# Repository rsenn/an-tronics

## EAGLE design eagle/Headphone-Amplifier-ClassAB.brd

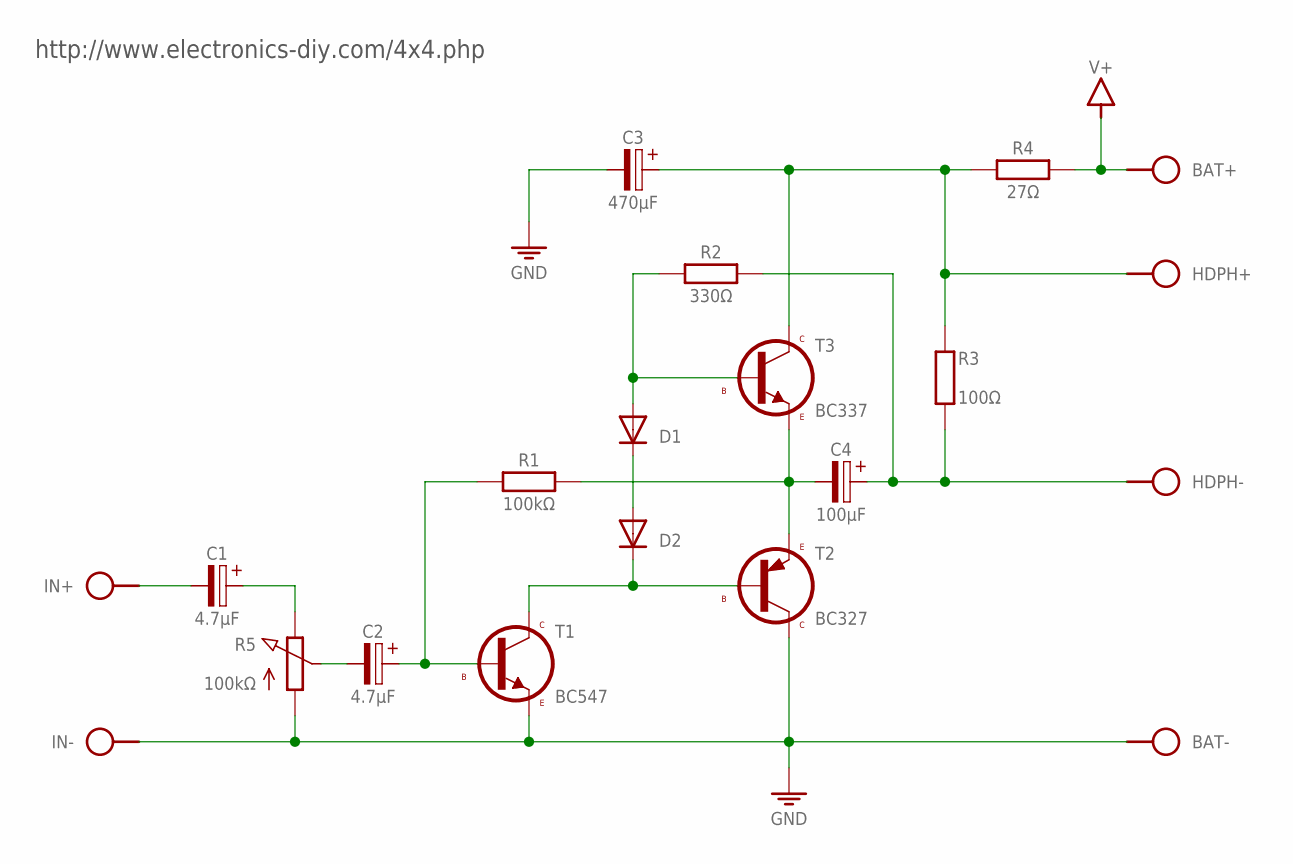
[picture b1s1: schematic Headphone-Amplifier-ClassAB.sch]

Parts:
BAT: SPAD+-+-; SPAD+-
C1, C2: 4.7μF; E2,5-4
C3: 470μF; E5-6
C4: 100μF; E5-4
D1, D2: 1N414834-5V; DO34-5V
HDPH: SPAD+--+; SPAD-+
IN: SPAD+--+; SPAD-+
R1: 100kΩ; 0202/7
R2: 330Ω; 0204/10
R3: 100Ω; 0204/10
R4: 27Ω; 0204V
R5: 100kΩ; CONN-3P
T1: BC547; TO92
T2: BC327; TO92
T3: BC337; TO92-CBE

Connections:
GND: BAT.1, C3.-, IN.1, R5.1 (A), T1.3 (E), T2.1 (C)
unnamed: D1.A, R2.1, T3.2 (B)
unnamed: D2.C, T1.1 (C), T2.2 (B)
unnamed: D1.C, D2.A
unnamed: C4.-, R1.2, T2.3 (E), T3.3 (E)
unnamed: C1.+, R5.3 (E)
unnamed: C2.-, R5.2 (S)
unnamed: C2.+, R1.1, T1.2 (B)
unnamed: C3.+, HDPH.2, R3.2 (1), R4.2 (1), T3.1 (C)
unnamed: C4.+, HDPH.1, R2.2, R3.1 (2)
unnamed: C1.-, IN.2
V+: BAT.2, R4.1 (2)

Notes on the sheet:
http://www.electronics-diy.com/4x4.php

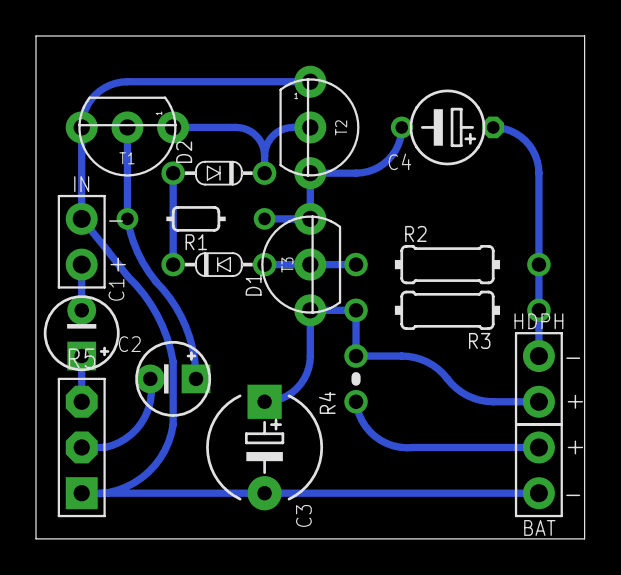
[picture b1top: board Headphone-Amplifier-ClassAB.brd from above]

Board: 2 copper layers, 30.5 x 27.9 mm, 17 parts (0 on the bottom side), 12 nets.

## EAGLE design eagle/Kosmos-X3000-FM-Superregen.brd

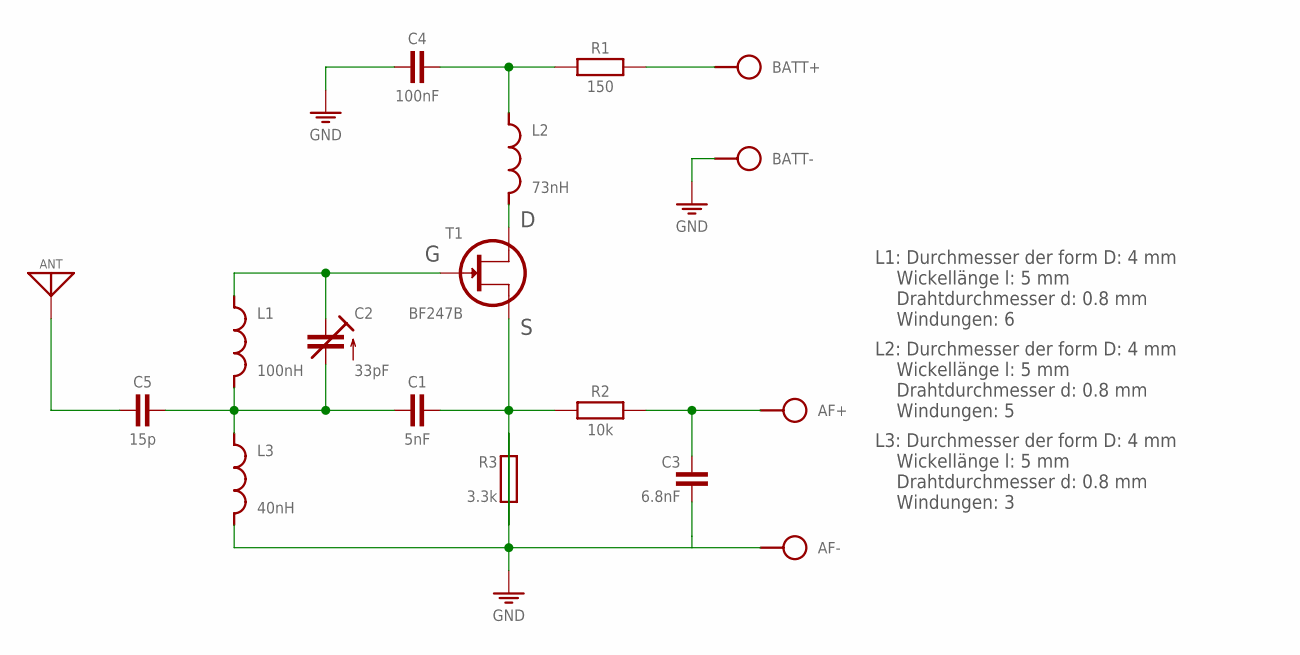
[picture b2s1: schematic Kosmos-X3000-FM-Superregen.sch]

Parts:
AF: SPAD+-+-; SPAD+-
ANT: ANT; SPAD
BATT: SPAD+-+-; SPAD+-
C1: 5nF; C050-020X044
C2: 33pF; TRIM-2222-808
C3: 6.8nF; C050-020X044
C4: 100nF; C050-020X044
C5: 15p; C025-015X024
L1: 100nH; L-04-5/5V
L2: 73nH; L-04-5/5V
L3: 40nH; L-04-5/5V
R1: 150; 0202/7-V
R2: 10k; 0202/7
R3: 3.3k; 0202/7
T1: BF247B; TO92

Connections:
GND: AF.1, BATT.1, C3.2, C4.2, L3.1, R3.2 (1)
unnamed: C2.1 (E), L1.2, T1.3 (G)
unnamed: C1.2, C2.2 (A), C5.1, L1.1, L3.2
unnamed: C4.1, L2.2, R1.1
unnamed: AF.2, C3.1, R2.2
unnamed: C1.1, R2.1, R3.1 (2), T1.2 (S)
unnamed: L2.1, T1.1 (D)
unnamed: BATT.2, R1.2
unnamed: ANT.1, C5.2

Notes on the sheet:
L2: Durchmesser der form D: 4 mm Wickellänge l: 5 mm Drahtdurchmesser d: 0.8 mm Windungen: 5
L3: Durchmesser der form D: 4 mm Wickellänge l: 5 mm Drahtdurchmesser d: 0.8 mm Windungen: 3
L1: Durchmesser der form D: 4 mm Wickellänge l: 5 mm Drahtdurchmesser d: 0.8 mm Windungen: 6

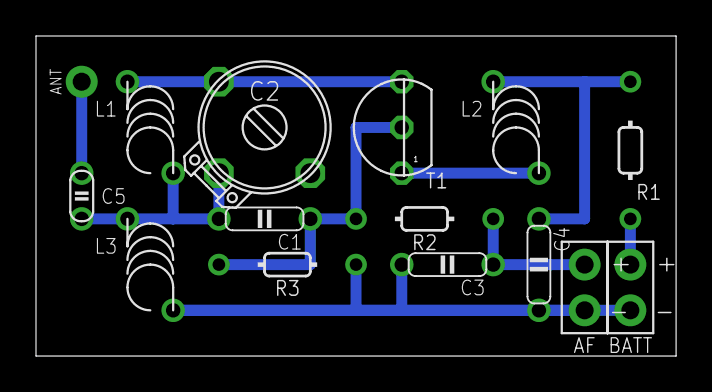
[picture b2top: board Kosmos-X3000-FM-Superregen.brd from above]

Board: 2 copper layers, 35.6 x 17.8 mm, 15 parts (0 on the bottom side), 9 nets.

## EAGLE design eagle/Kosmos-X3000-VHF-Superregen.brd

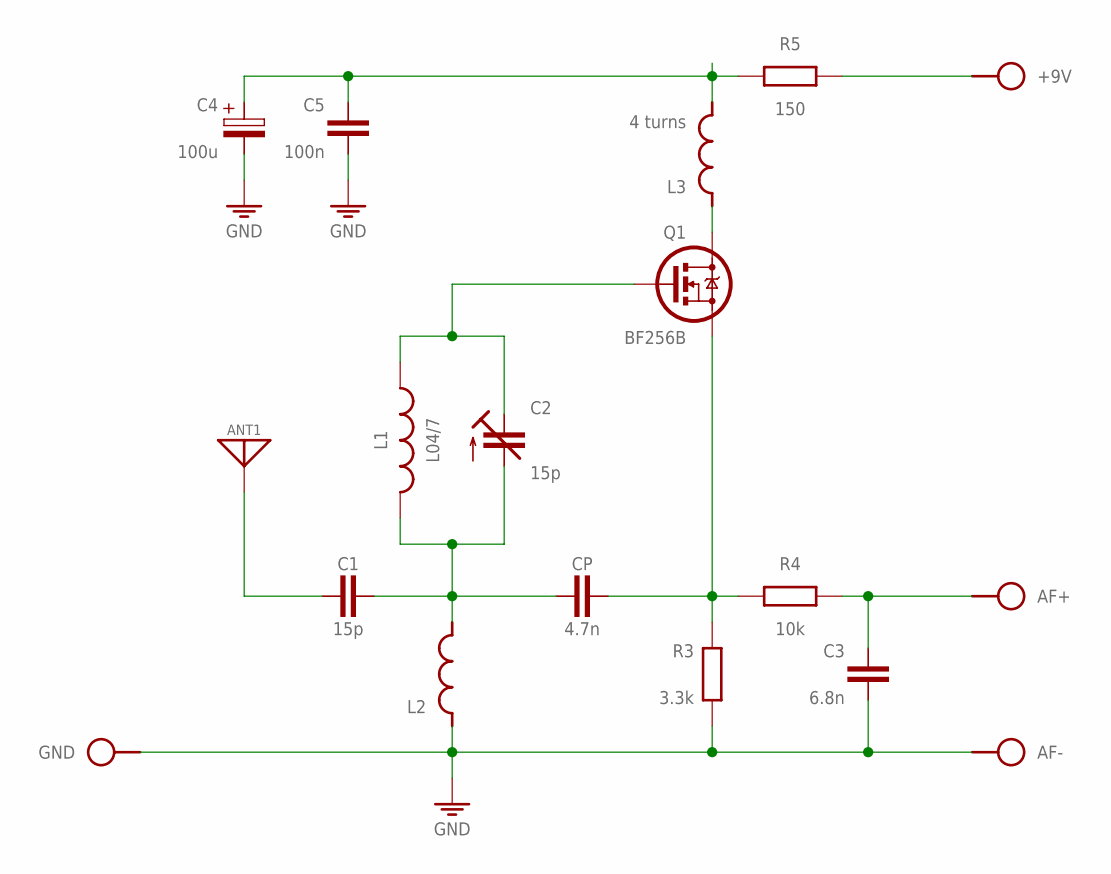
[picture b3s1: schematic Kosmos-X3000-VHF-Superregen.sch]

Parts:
+9V: SPAD
AF+: SPAD
AF-: SPAD
ANT1: ANT; SPAD
C1: 15p; C025-015X024
C2: 15p; TRIM-2222-808
C3: 6.8n; C050-020X036
C4: 100u; E2.5-4/V
C5: 100n; C025-015X024
CP: 4.7n; C025-015X024
GND: SPAD
L1: L04/7; L-04/7V
L2: L-SHORT04-5/5V; L-04-5/5V
L3: 4 turns; L-04-5/5V
Q1: BF256B; TO92
R3: 3.3k; 0204/10
R4: 10k; 0204/10
R5: 150; 0204/10

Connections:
GND: AF-.1, C3.2, C4.-, C5.2, GND.1, L2.2, R3.1
unnamed: CP.1, Q1.2 (S), R3.2, R4.1
unnamed: AF+.1, C3.1, R4.2
unnamed: ANT1.1, C1.2
unnamed: C4.+, C5.1, L3.1, R5.1
unnamed: C2.3 (E), L1.2 (1), Q1.1 (G)
unnamed: C1.1, C2.2 (A), CP.2, L1.1 (2), L2.1
unnamed: L3.2, Q1.3 (D)
unnamed: +9V.1, R5.2

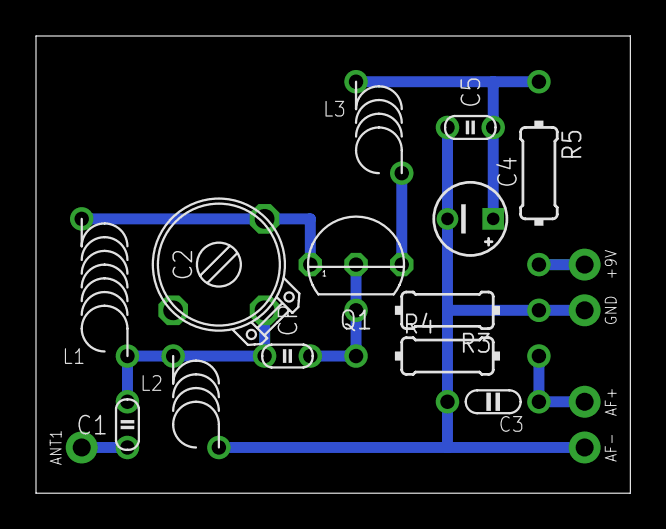
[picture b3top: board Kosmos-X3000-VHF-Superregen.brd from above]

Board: 2 copper layers, 33.0 x 25.4 mm, 18 parts (0 on the bottom side), 9 nets.

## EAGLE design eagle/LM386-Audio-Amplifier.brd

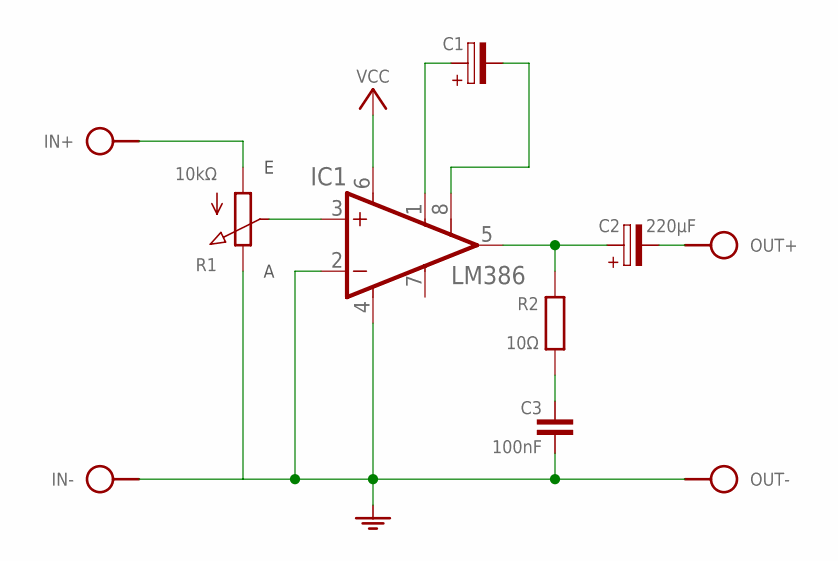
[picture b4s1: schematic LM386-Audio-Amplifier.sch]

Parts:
C1: CPOL-HE2,5-3; E2,5-3
C2: 220µF; E5-5
C3: 100nF; C050-020X044
IC1: LM386; DIL08
IN: SPAD+-+-; SPAD+-
OUT: SPAD+--+; SPAD-+
R1: 10kΩ; CONN-3P
R2: 10Ω; 0204/10-V
S1: 4-12V; PWR-R

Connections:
GND: C3.2, IC1.2 (-IN), IC1.4 (GND), IN.1, OUT.1, R1.3 (E), S1.1 (GND)
unnamed: IC1.3 (+IN), R1.2 (S)
unnamed: IN.2, R1.1 (A)
unnamed: C1.+, IC1.1 (GAIN)
unnamed: C1.-, IC1.8 (GAIN)
unnamed: C3.1, R2.2 (1)
unnamed: C2.+, IC1.5 (OUT), R2.1 (2)
unnamed: C2.-, OUT.2
VCC: IC1.6 (VS), S1.2 (VCC)

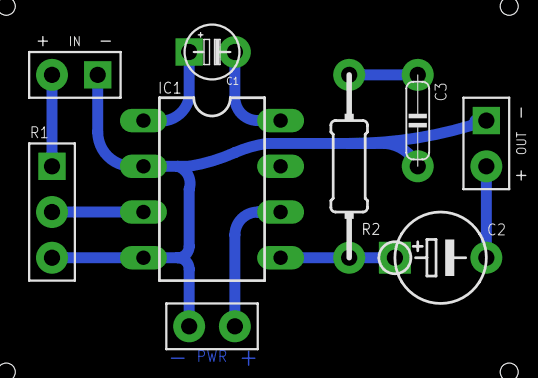
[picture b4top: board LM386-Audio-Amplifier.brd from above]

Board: 2 copper layers, 9 parts (0 on the bottom side), 9 nets.

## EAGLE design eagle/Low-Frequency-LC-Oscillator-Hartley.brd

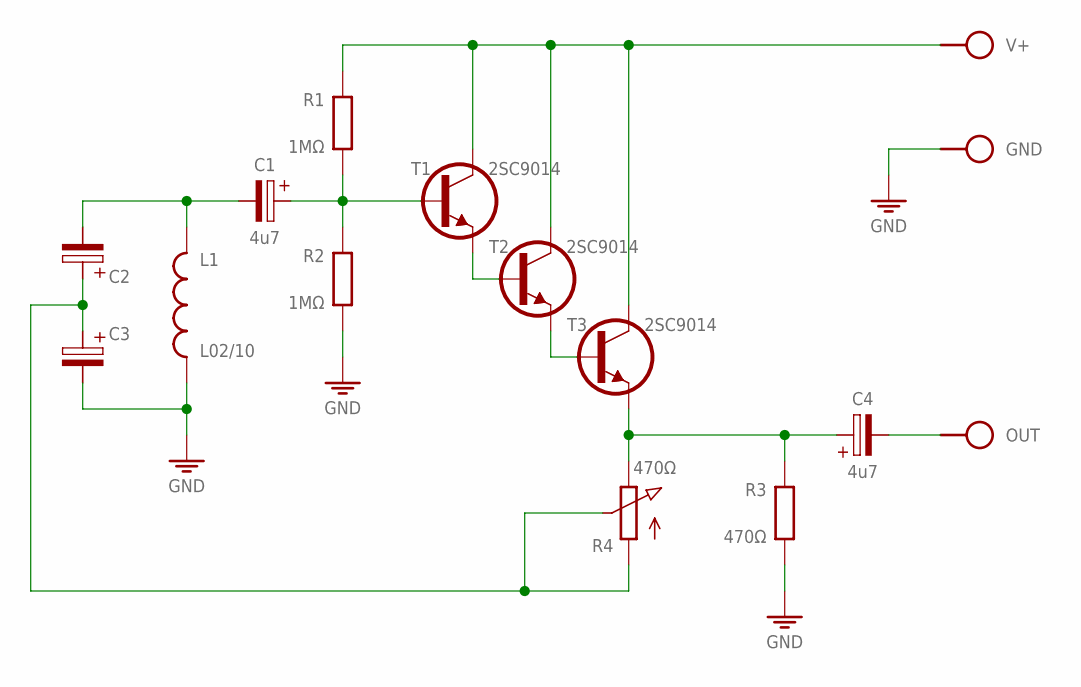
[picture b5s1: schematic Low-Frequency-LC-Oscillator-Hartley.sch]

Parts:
C1, C4: 4u7; E2,5-3
C2, C3: CPOLE2.5-5; E2,5-5
GND: SPAD
L1: L02/10; L-03/10V
OUT: SPAD
R1: 1MΩ; 0204/15
R2: 1MΩ; 0204/12-V
R3: 470Ω; 0204/12
R4: 470Ω; POT
T1, T2, T3: 2SC9014; TO92-EBC
V+: SPAD

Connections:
GND: C3.-, GND.1, L1.2, R2.1, R3.1
unnamed: R1.2, T1.C, T2.C, T3.C, V+.1
unnamed: C4.-, OUT.1
unnamed: C4.+, R3.2, R4.3 (E), T3.E
unnamed: T1.E, T2.B
unnamed: T2.E, T3.B
unnamed: C1.-, C2.-, L1.1
unnamed: C1.+, R1.1, R2.2, T1.B
unnamed: C2.+, C3.+, R4.1 (A), R4.2 (S)

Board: 2 copper layers, 15 parts (0 on the bottom side), 9 nets, no tracks yet.

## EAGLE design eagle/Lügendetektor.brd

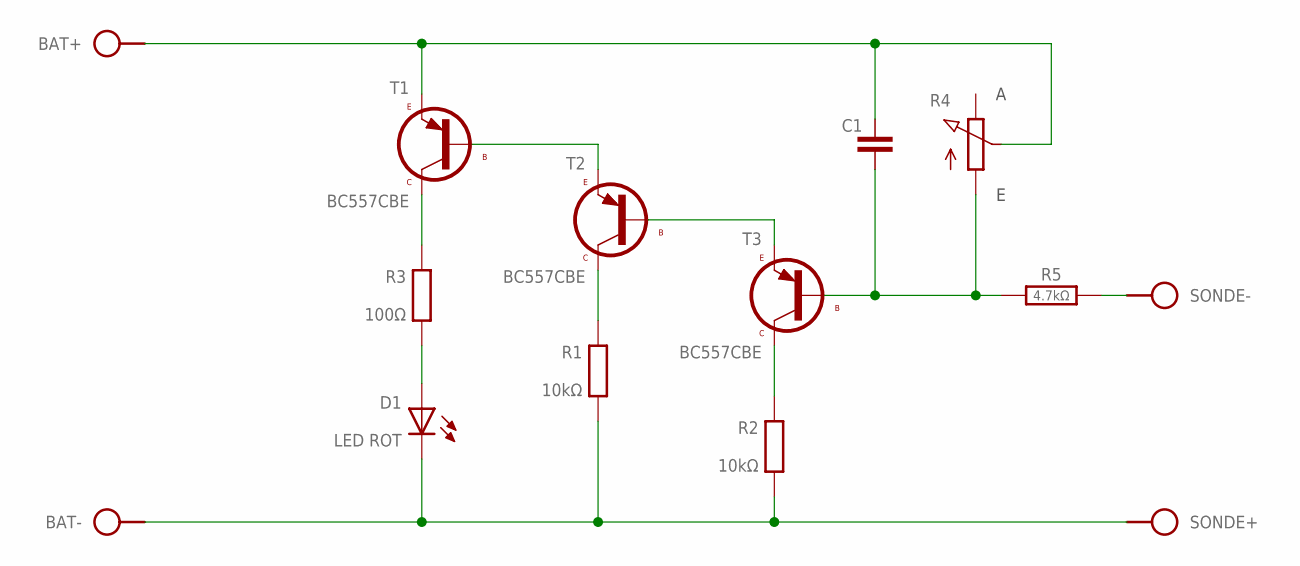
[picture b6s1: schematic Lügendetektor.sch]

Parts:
BAT: SPAD+-+-; SPAD+-
C1: C050-020X044/V
D1: LED ROT; LED_3MM/V
R1, R2: 10kΩ; 0204/10-V
R3: 100Ω; 0204/10-V
R4: POT-V
R5: 4.7kΩ; 0204/10
SONDE: SPAD+-+-; SPAD+-
T1, T2, T3: BC557CBE; TO92-CBE

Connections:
unnamed: R3.1 (2), T1.1 (C)
unnamed: D1.A, R3.2 (1)
unnamed: R1.1 (2), T2.1 (C)
unnamed: R2.1 (2), T3.1 (C)
unnamed: BAT.1, D1.K (C), R1.2 (1), R2.2 (1), SONDE.2
unnamed: BAT.2, C1.1, R4.S, T1.3 (E)
unnamed: T1.2 (B), T2.3 (E)
unnamed: T2.2 (B), T3.3 (E)
unnamed: R5.2, SONDE.1
unnamed: C1.2, R4.A, R5.1, T3.2 (B)

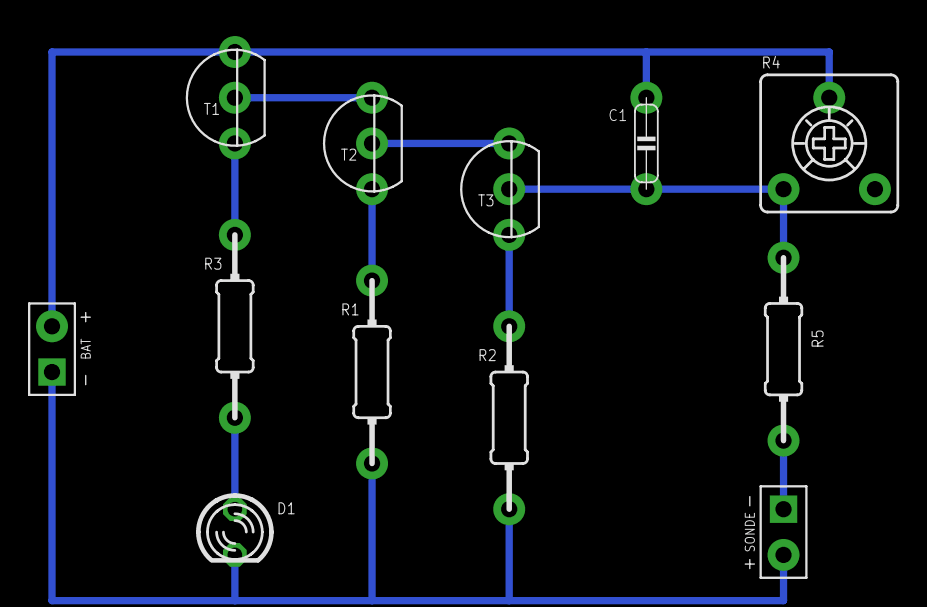
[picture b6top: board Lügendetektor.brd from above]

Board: 2 copper layers, 12 parts (0 on the bottom side), 10 nets.

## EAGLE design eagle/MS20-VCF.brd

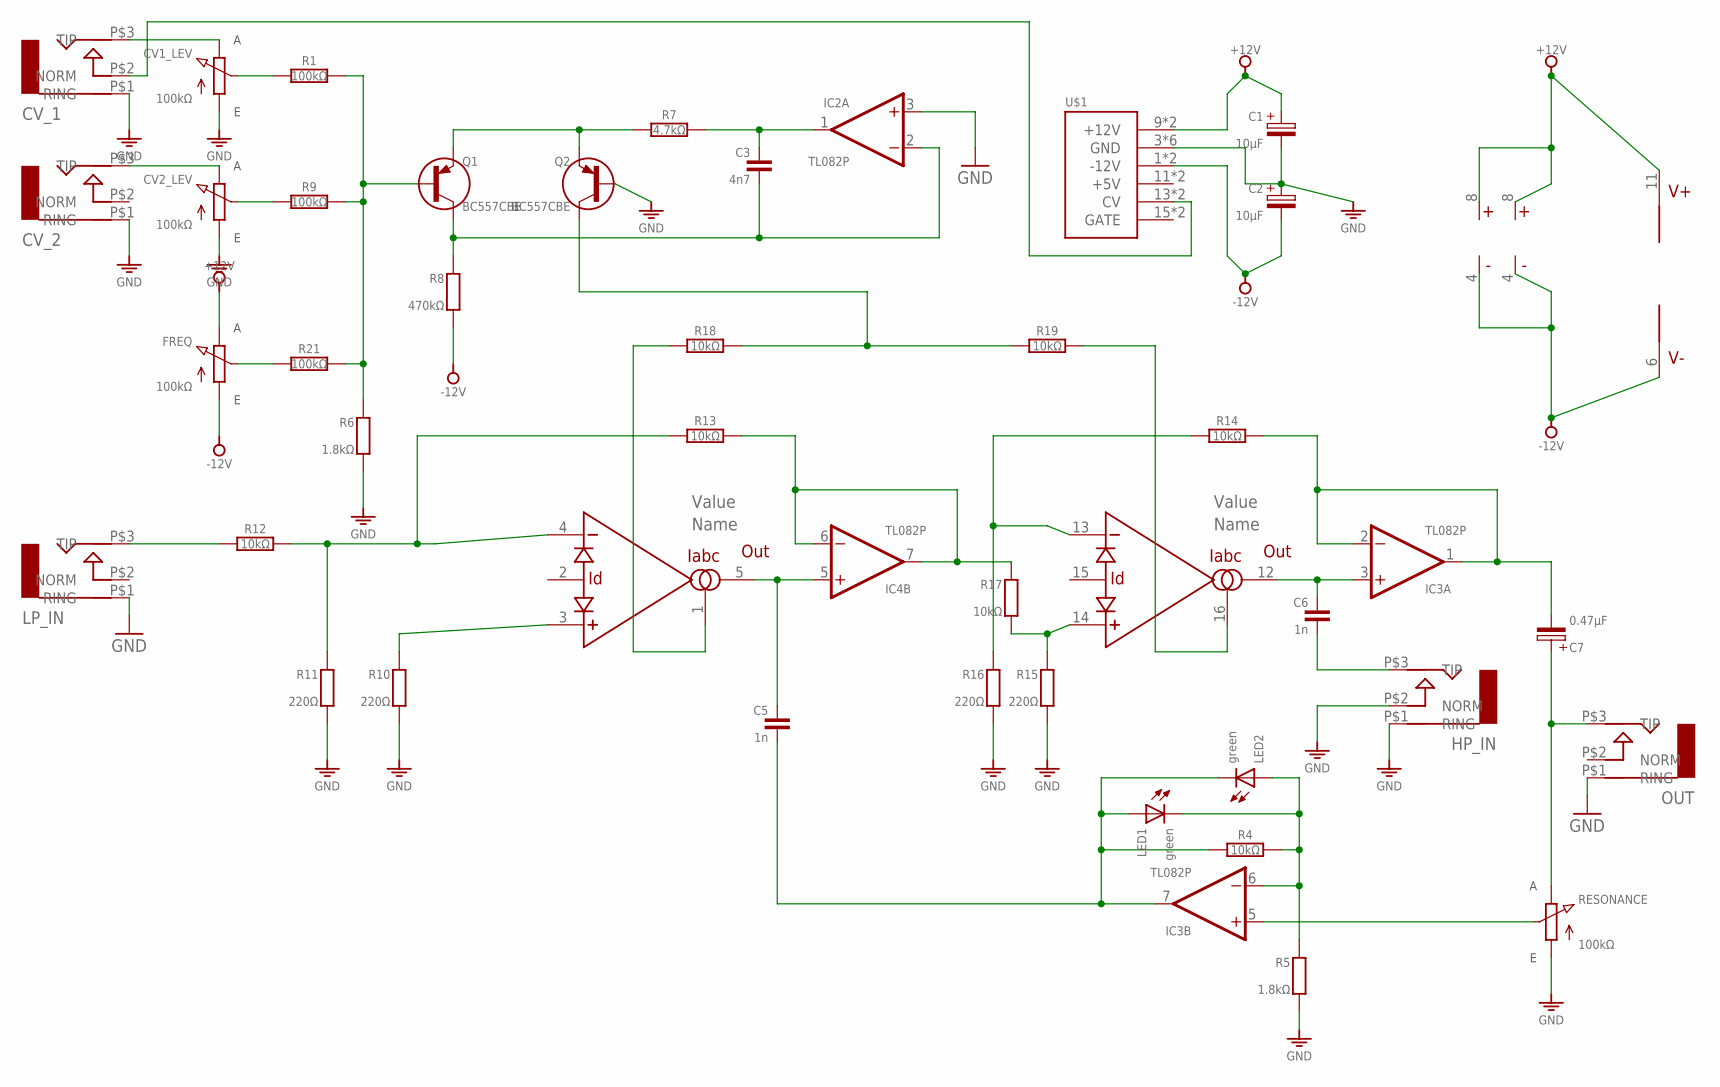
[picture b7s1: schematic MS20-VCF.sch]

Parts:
C1, C2: 10μF; E2,5-5/V
C3: 4n7; C050-020X036/V
C5, C6: 1n; C050-020X036/V
C7: 0.47μF; E2,5-5/V
CV1_LEV, CV2_LEV: 100kΩ; POT-V
CV_1, CV_2: AUDIO-JACK; ERTHENVAR-JACK-90DEG
FREQ: 100kΩ; POT
HP_IN: AUDIO-JACK; ERTHENVAR-JACK-90DEG
IC1: LM13700; DIL16
IC2, IC3, IC4: TL082P; DIL08
LED1, LED2: green; LED_3MM
LP_IN: AUDIO-JACK; ERTHENVAR-JACK-90DEG
OUT: AUDIO-JACK; ERTHENVAR-JACK-90DEG
Q1, Q2: BC557CBE; TO92-CBE
R1, R9, R21: 100kΩ; 0204/10
R4, R12, R18: 10kΩ; 0204/10
R5, R6: 1.8kΩ; 0204/10-V
R7: 4.7kΩ; 0204/10
R8: 470kΩ; 0204/10-V
R10, R11, R15, R16: 220Ω; 0204/10-V
R13, R14, R17, R19: 10kΩ; 0204/10-V
RESONANCE: 100kΩ; POT
U$1: POWER; POWER_16

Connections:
+12V: C1.+, FREQ.E, IC1.11 (V+), IC2.8 (V+), IC3.8 (V+), U$1.9 (+12V), U$1.10 (+12V)
-12V: C2.-, FREQ.A, IC1.6 (V-), IC2.4 (V-), IC3.4 (V-), R8.2 (1), U$1.1 (-12V), U$1.2 (-12V)
GND: C1.-, C2.+, CV1_LEV.A, CV2_LEV.A, CV_1.P$1 (RING), CV_2.P$1 (RING), HP_IN.P$1 (RING), HP_IN.P$2 (NORM), IC2.3 (+IN), LP_IN.P$1 (RING), OUT.P$1 (RING), Q2.B, R5.2 (1), R6.2 (1), R10.2 (1), R11.2 (1), R15.2 (1), R16.2 (1), RESONANCE.A, U$1.3 (GND), U$1.4 (GND), U$1.5 (GND), U$1.6 (GND), U$1.7 (GND), U$1.8 (GND)
unnamed: IC3.6 (-IN), LED1.K (C), LED2.A, R4.2, R5.1 (2)
unnamed: C5.2, IC3.7 (OUT), LED1.A, LED2.K (C), R4.1
unnamed: C3.2, IC2.2 (-IN), Q1.C, R8.1 (2)
unnamed: C3.1, IC2.1 (OUT), R7.2
unnamed: Q1.E, Q2.E, R7.1
unnamed: IC3.5 (+IN), RESONANCE.S
unnamed: CV1_LEV.S, R1.1
unnamed: CV2_LEV.S, R9.1
unnamed: C5.1, IC1.5 (OUT), IC4.5 (+IN)
unnamed: C6.1, IC1.12 (OUT), IC3.3 (+IN)
unnamed: C7.-, IC3.1 (OUT), IC3.2 (-IN), R14.2
unnamed: C7.+, OUT.P$3 (TIP), RESONANCE.E
unnamed: IC1.1 (IABC), R18.1
unnamed: IC1.4 (-IN), R11.1 (2), R12.2, R13.1
unnamed: IC1.3 (+IN), R10.1 (2)
unnamed: Q2.C, R18.2, R19.1
unnamed: IC1.16 (IABC), R19.2
unnamed: IC1.13 (-IN), R14.1, R16.1 (2)
unnamed: IC4.6 (-IN), IC4.7 (OUT), R13.2, R17.1 (2)
unnamed: IC1.14 (+IN), R15.1 (2), R17.2 (1)
unnamed: Q1.B, R1.2, R6.1 (2), R9.2, R21.2
unnamed: FREQ.S, R21.1
unnamed: CV2_LEV.E, CV_2.P$3 (TIP)
unnamed: CV1_LEV.E, CV_1.P$3 (TIP)
unnamed: LP_IN.P$3 (TIP), R12.1
unnamed: C6.2, HP_IN.P$3 (TIP)
unnamed: CV_1.P$2 (NORM), U$1.13 (CV), U$1.14 (CV)
V+: IC4.8 (V+)
V-: IC4.4 (V-)

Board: 2 copper layers, 42 parts (0 on the bottom side), 30 nets, no tracks yet.
